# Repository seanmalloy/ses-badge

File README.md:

# ses-badge

A simple blinking LED badge designed with KiCad.

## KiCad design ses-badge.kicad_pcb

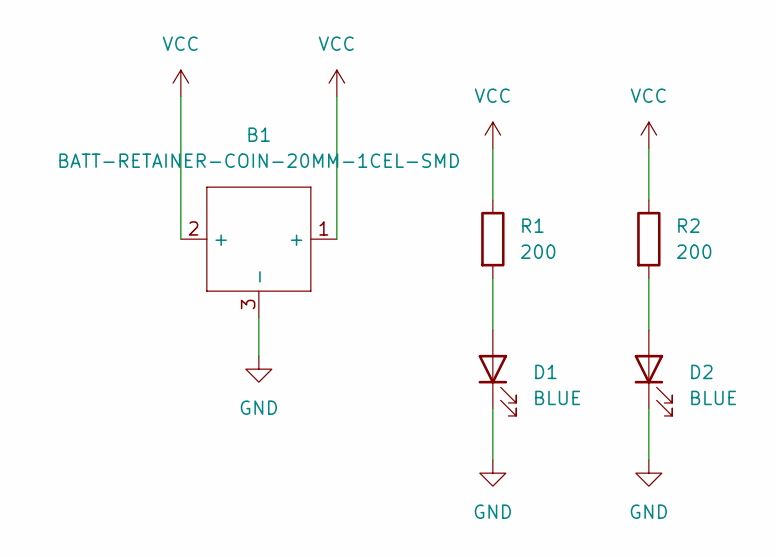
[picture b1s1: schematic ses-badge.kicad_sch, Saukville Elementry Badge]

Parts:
B1: BATT-RETAINER-COIN-20MM-1CEL-SMD
D1, D2: BLUE; LED_D5.0mm
R1, R2: 200; R_Axial_DIN0204_L3.6mm_D1.6mm_P5.08mm_Horizontal

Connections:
GND: B1.3 (-), D1.1 (K), D2.1 (K)
unnamed: D1.2 (A), R1.2
unnamed: D2.2 (A), R2.2
VCC: B1.1 (+), B1.2 (+), R1.1, R2.1

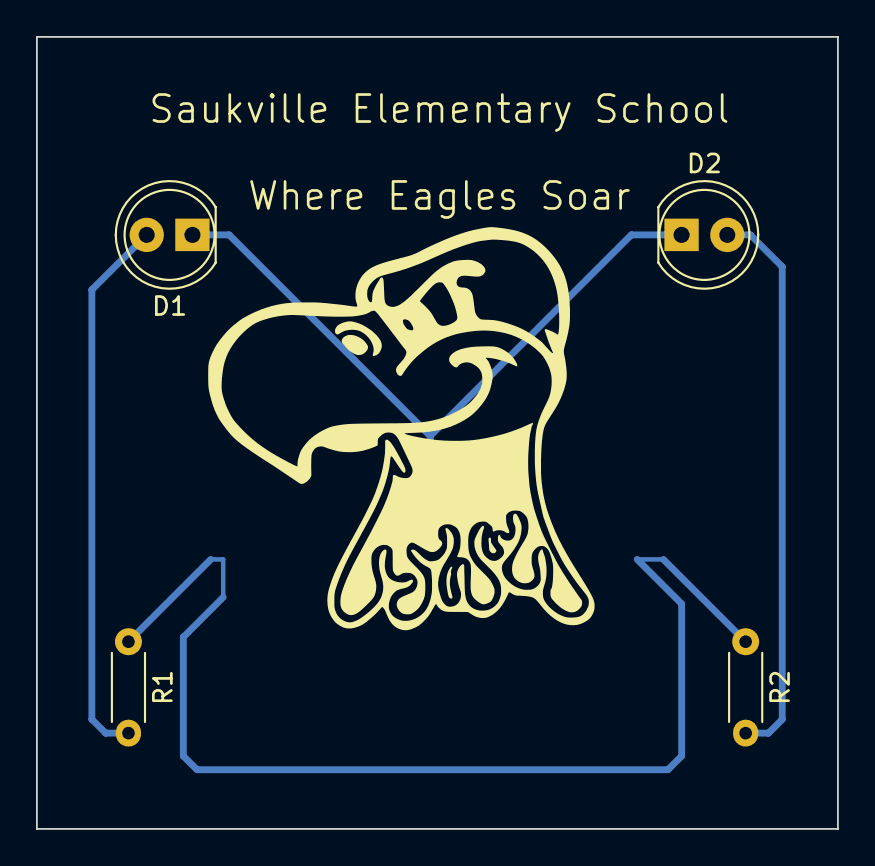
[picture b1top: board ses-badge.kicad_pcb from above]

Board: 2 copper layers, 44.5 x 44.0 mm, 5 parts (1 on the bottom side), 4 nets.

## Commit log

2022-08-20 Do Not Included Zip Files
2022-08-26 Update Gerber Files From Latest PCB Layout
2022-08-26 Add License

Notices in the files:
ses-badge.kicad_sch:
creativecommons.org/licenses/by/4.0
License: CC by 4.0
